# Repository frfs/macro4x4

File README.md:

# macro4x4
4x4 size macro keyboard

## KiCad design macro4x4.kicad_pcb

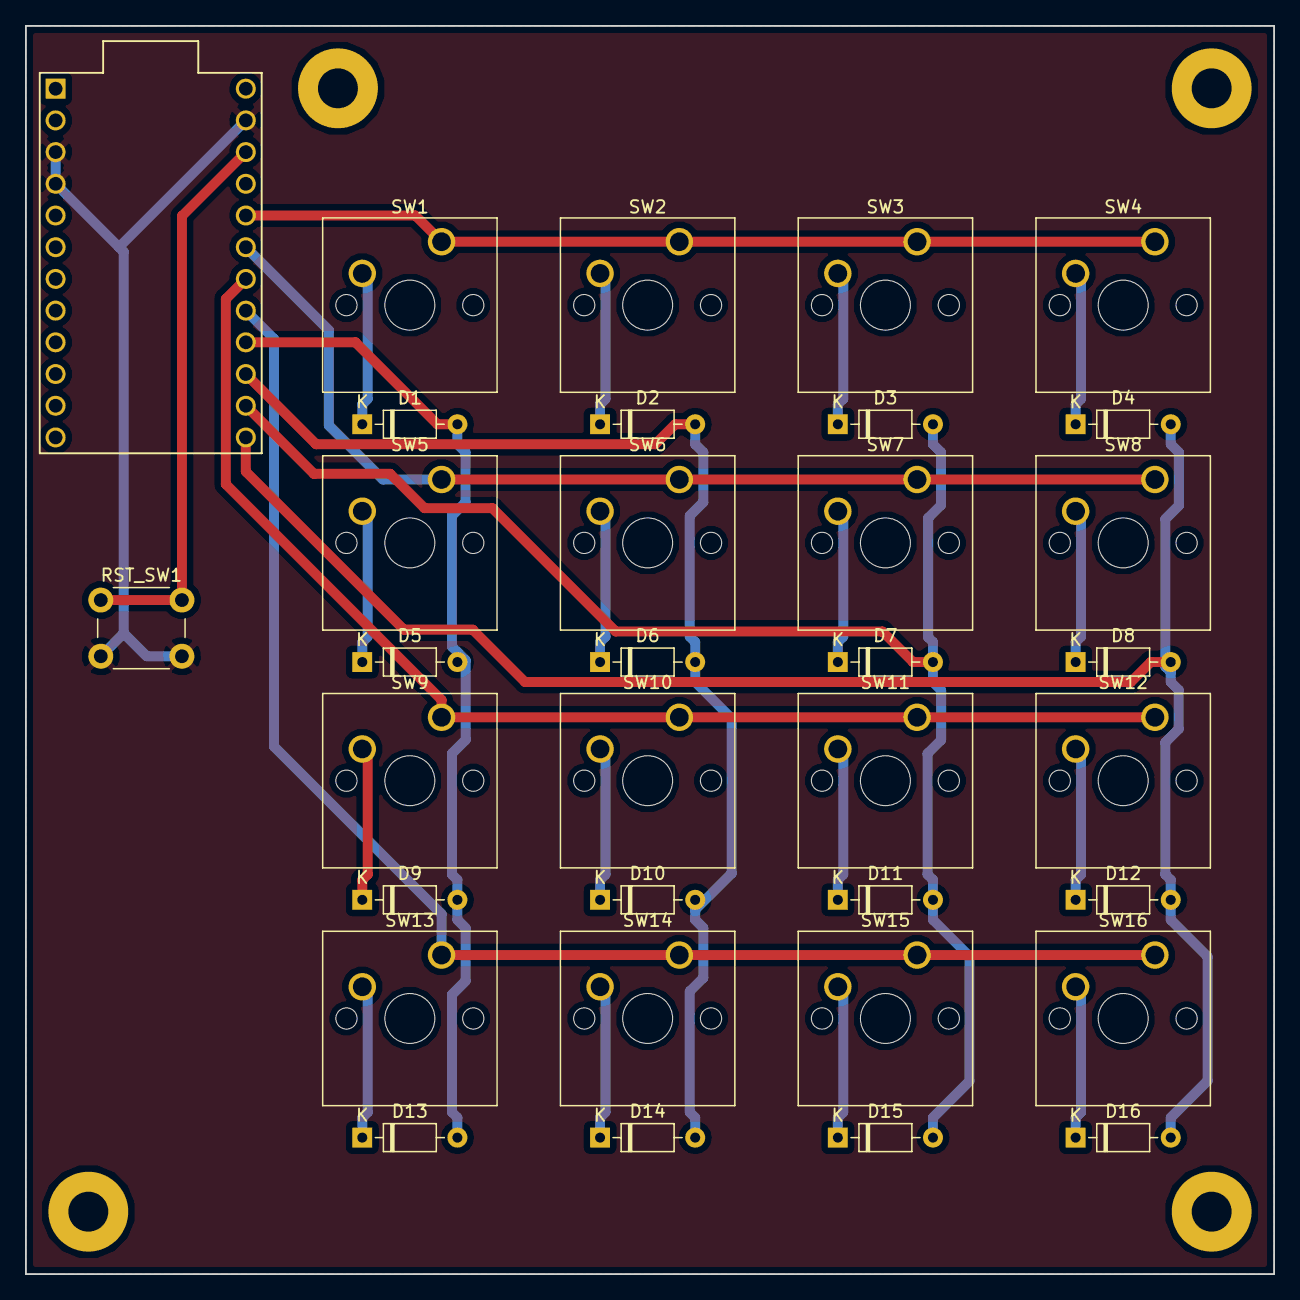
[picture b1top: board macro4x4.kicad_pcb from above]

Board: 2 copper layers, 100.0 x 100.0 mm, 38 parts (0 on the bottom side), 26 nets.

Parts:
D1, D2, D3, D4, D5, D6, D7, D8, D9, D10, D11, D12, D13, D14, D15, D16: DIODE; D_DO-35_SOD27_P7.62mm_Horizontal
RST_SW1: RST_SW; SW_PUSH_6mm
SW1, SW2, SW3, SW4, SW5, SW6, SW7, SW8, SW9, SW10, SW11, SW12, SW13, SW14, SW15, SW16: SW_Push; SW_Cherry_MX1A_1.00u_PCB
U1: ProMicro
m1, m2, m3, m4: MountingHole_3.2mm_M3_Pad

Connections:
COL0: D1.2, D5.2, D9.2, D13.2, U1.16
COL1: D2.2, D6.2, D10.2, D14.2, U1.15
COL2: D3.2, D7.2, D11.2, D15.2, U1.14
COL3: D4.2, D8.2, D12.2, D16.2, U1.13
GND: RST_SW1.2, U1.3, U1.4, U1.23
unnamed: D1.1, SW1.2
unnamed: D2.1, SW2.2
unnamed: D3.1, SW3.2
unnamed: D4.1, SW4.2
unnamed: D5.1, SW5.2
unnamed: D6.1, SW6.2
unnamed: D7.1, SW7.2
unnamed: D8.1, SW8.2
unnamed: D9.1, SW9.2
unnamed: D10.1, SW10.2
unnamed: D11.1, SW11.2
unnamed: D12.1, SW12.2
unnamed: D13.1, SW13.2
unnamed: D14.1, SW14.2
unnamed: D15.1, SW15.2
unnamed: D16.1, SW16.2
unnamed: RST_SW1.1, U1.22
ROW0: SW1.1, SW2.1, SW3.1, SW4.1, U1.20
ROW1: SW5.1, SW6.1, SW7.1, SW8.1, U1.19
ROW2: SW9.1, SW10.1, SW11.1, SW12.1, U1.18
ROW3: SW13.1, SW14.1, SW15.1, SW16.1, U1.17

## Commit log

2018-09-07 mod gitignore
2018-09-07 Create LICENSE
2018-09-07 フットプリントのパスを修正
2018-09-07 ・回路図を修正 ・基板でビアを使用しないように修正
2018-09-07 回路図出力
